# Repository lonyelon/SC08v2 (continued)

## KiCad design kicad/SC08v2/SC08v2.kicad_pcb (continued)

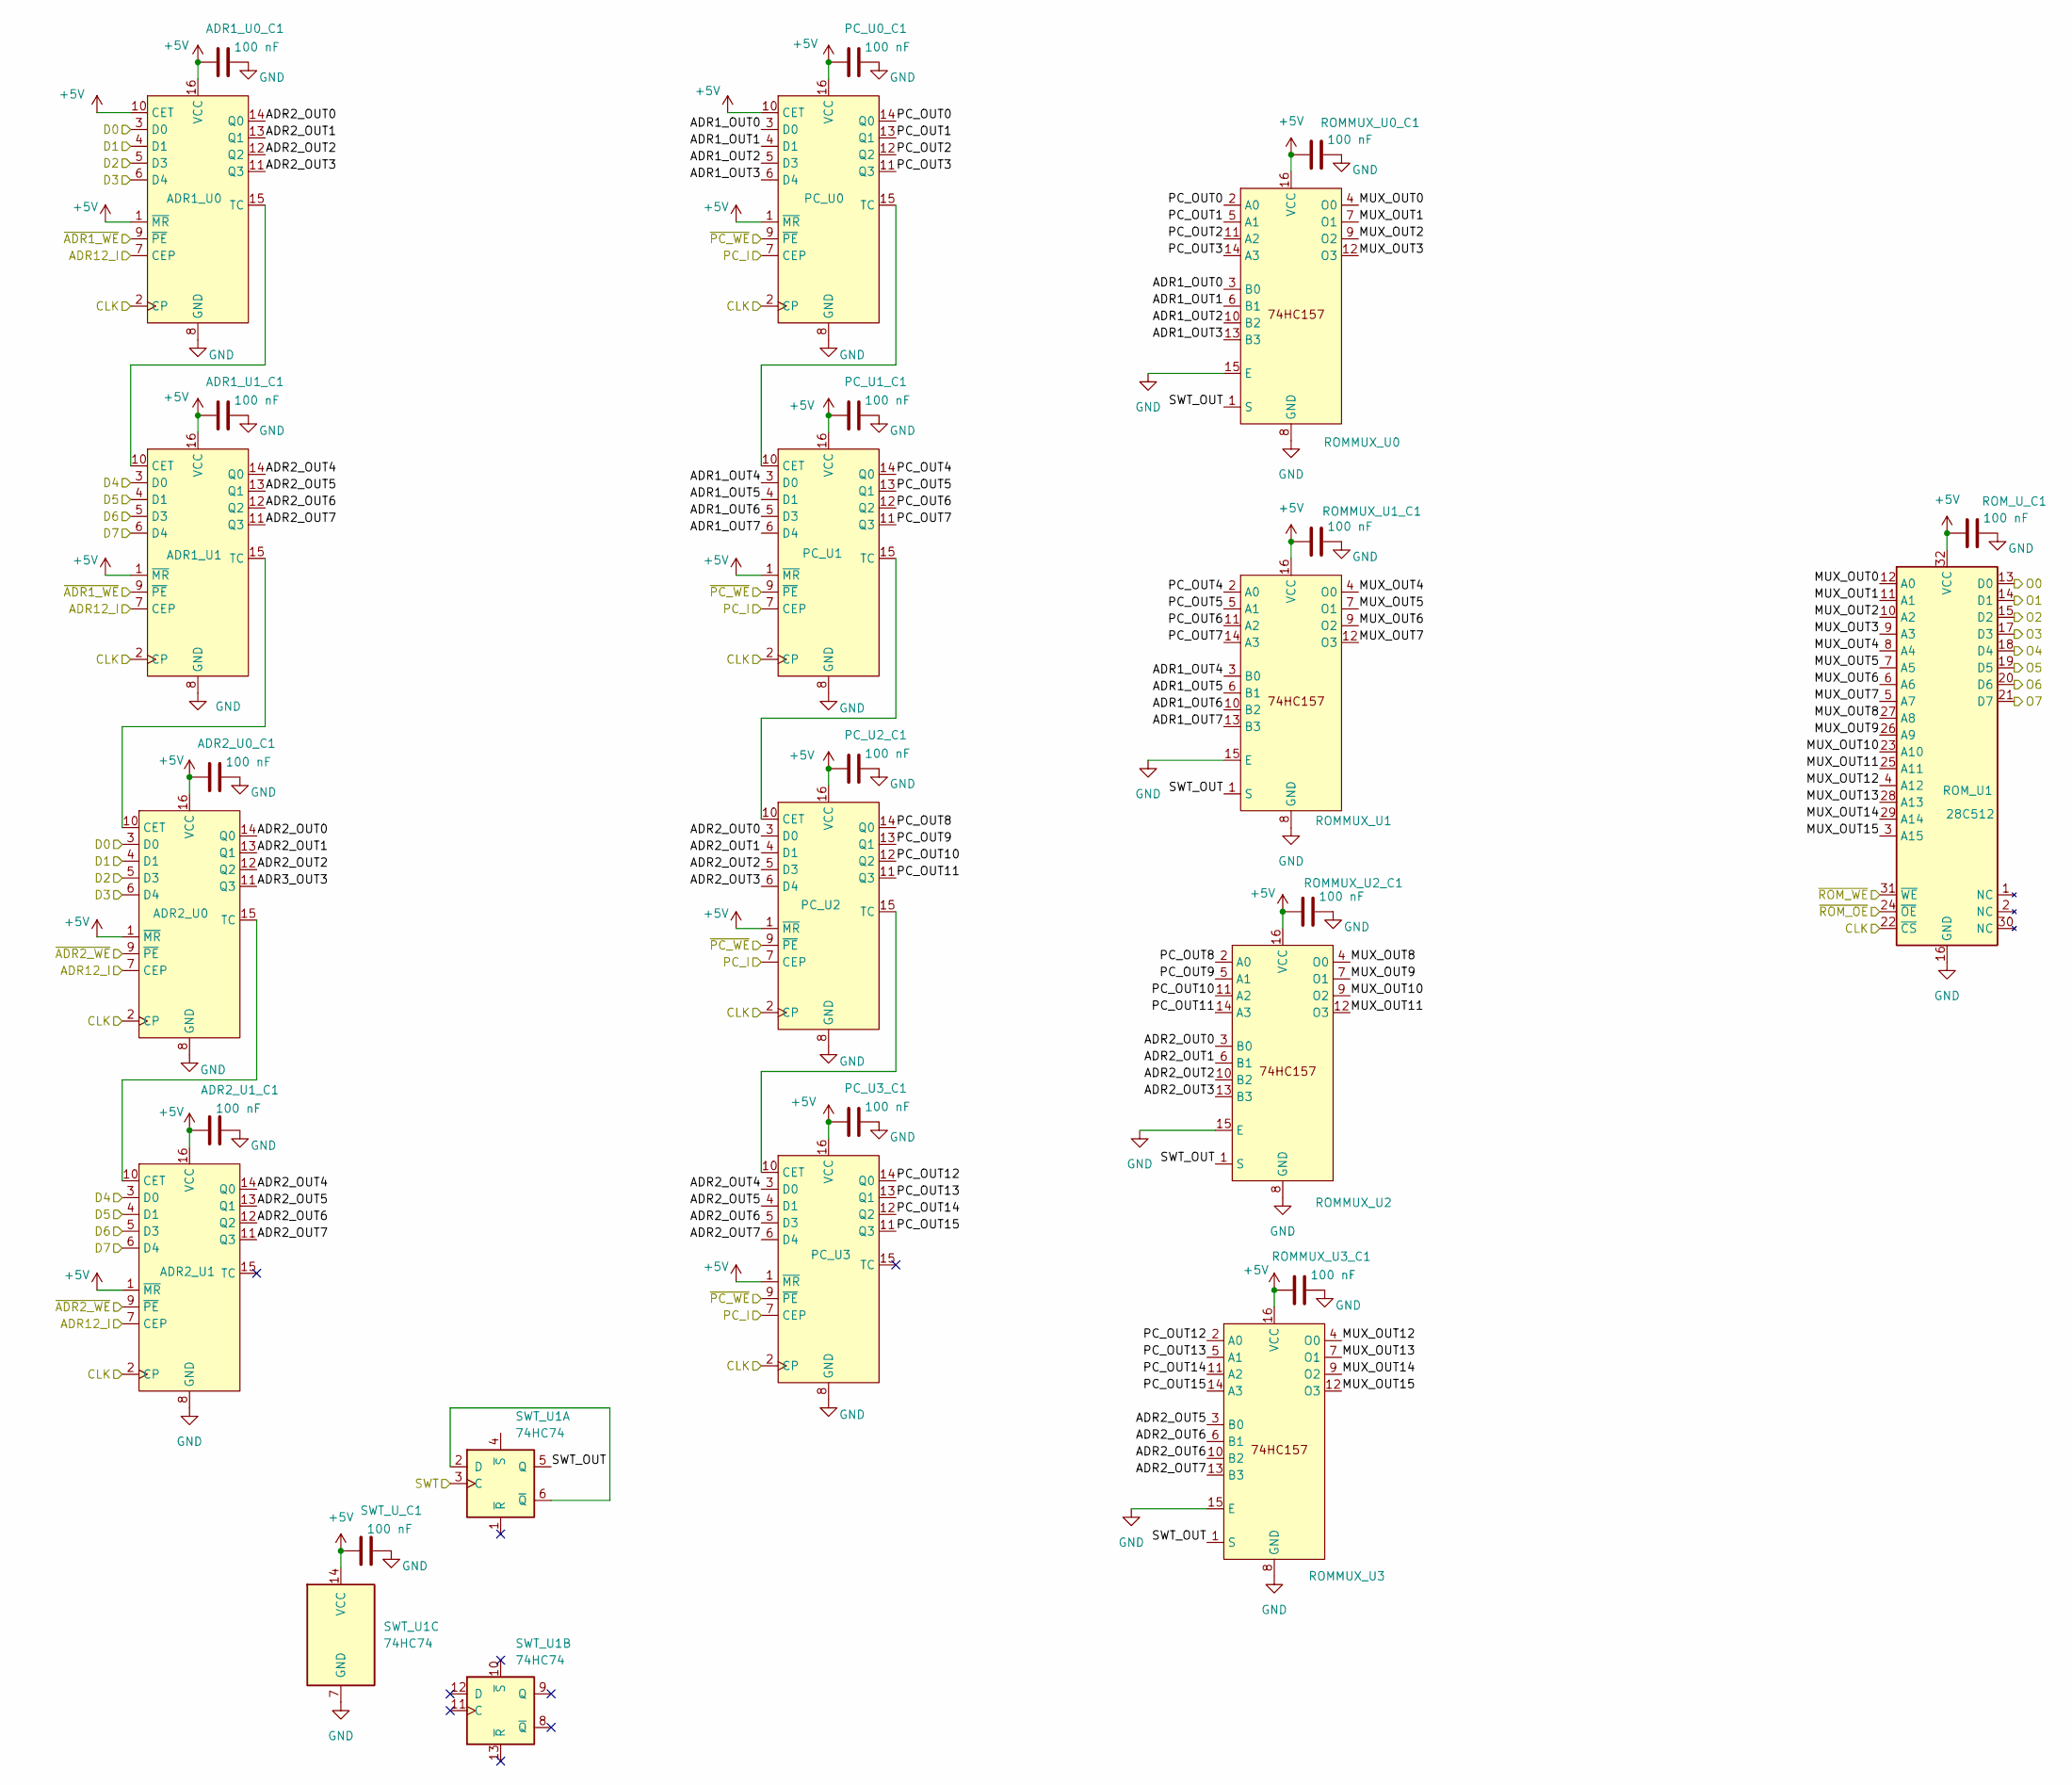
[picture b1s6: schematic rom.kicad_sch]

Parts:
ADR1_U0, ADR1_U1, ADR2_U0, ADR2_U1: DIP-16_W7.62mm
ADR1_U0_C1, ADR1_U1_C1, ADR2_U0_C1, ADR2_U1_C1: 100 nF; C_Disc_D3.0mm_W1.6mm_P2.50mm
PC_U0, PC_U1, PC_U2, PC_U3: DIP-16_W7.62mm
PC_U0_C1, PC_U1_C1, PC_U2_C1, PC_U3_C1: 100 nF; C_Disc_D3.0mm_W1.6mm_P2.50mm
ROMMUX_U0, ROMMUX_U1, ROMMUX_U2, ROMMUX_U3: DIP-16_W7.62mm
ROMMUX_U0_C1, ROMMUX_U1_C1, ROMMUX_U2_C1, ROMMUX_U3_C1: 100 nF; C_Disc_D3.0mm_W1.6mm_P2.50mm
ROM_U1: 28C512; DIP-32_W15.24mm
ROM_U_C1: 100 nF; C_Disc_D3.0mm_W1.6mm_P2.50mm
SWT_U1: 74HC74; DIP-14_W7.62mm
SWT_U_C1: 100 nF; C_Disc_D3.0mm_W1.6mm_P2.50mm

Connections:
+5V: ADR1_U0.1 (~MR), ADR1_U0.10 (CET), ADR1_U0.16 (VCC), ADR1_U0_C1.1, ADR1_U1.1 (~MR), ADR1_U1.16 (VCC), ADR1_U1_C1.1, ADR2_U0.1 (~MR), ADR2_U0.16 (VCC), ADR2_U0_C1.1, ADR2_U1.1 (~MR), ADR2_U1.16 (VCC), ADR2_U1_C1.1, PC_U0.1 (~MR), PC_U0.10 (CET), PC_U0.16 (VCC), PC_U0_C1.1, PC_U1.1 (~MR), PC_U1.16 (VCC), PC_U1_C1.1, PC_U2.1 (~MR), PC_U2.16 (VCC), PC_U2_C1.1, PC_U3.1 (~MR), PC_U3.16 (VCC), PC_U3_C1.1, ROMMUX_U0.16 (VCC), ROMMUX_U0_C1.1, ROMMUX_U1.16 (VCC), ROMMUX_U1_C1.1, ROMMUX_U2.16 (VCC), ROMMUX_U2_C1.1, ROMMUX_U3.16 (VCC), ROMMUX_U3_C1.1, ROM_U1.32 (VCC), ROM_U_C1.1, SWT_U1.14 (VCC), SWT_U_C1.1; also elsewhere on the board
/ADR12_I: ADR1_U0.7 (CEP), ADR1_U1.7 (CEP), ADR2_U0.7 (CEP), ADR2_U1.7 (CEP); also elsewhere on the board
/BUS_0: ADR1_U0.3 (D0), ADR2_U0.3 (D0), ROM_U1.13 (D0); also elsewhere on the board
/BUS_1: ADR1_U0.4 (D1), ADR2_U0.4 (D1), ROM_U1.14 (D1); also elsewhere on the board
/BUS_2: ADR1_U0.5 (D3), ADR2_U0.5 (D3), ROM_U1.15 (D2); also elsewhere on the board
/BUS_3: ADR1_U0.6 (D4), ADR2_U0.6 (D4), ROM_U1.17 (D3); also elsewhere on the board
/BUS_4: ADR1_U1.3 (D0), ADR2_U1.3 (D0), ROM_U1.18 (D4); also elsewhere on the board
/BUS_5: ADR1_U1.4 (D1), ADR2_U1.4 (D1), ROM_U1.19 (D5); also elsewhere on the board
/BUS_6: ADR1_U1.5 (D3), ADR2_U1.5 (D3), ROM_U1.20 (D6); also elsewhere on the board
/BUS_7: ADR1_U1.6 (D4), ADR2_U1.6 (D4), ROM_U1.21 (D7); also elsewhere on the board
/CLK: ADR1_U0.2 (CP), ADR1_U1.2 (CP), ADR2_U0.2 (CP), ADR2_U1.2 (CP), PC_U0.2 (CP), PC_U1.2 (CP), PC_U2.2 (CP), PC_U3.2 (CP), ROM_U1.22 (~CS); also elsewhere on the board
/PC_I: PC_U0.7 (CEP), PC_U1.7 (CEP), PC_U2.7 (CEP), PC_U3.7 (CEP); also elsewhere on the board
/ROM/ADR1_OUT0: PC_U0.3 (D0), ROMMUX_U0.3 (B0)
/ROM/ADR1_OUT1: PC_U0.4 (D1), ROMMUX_U0.6 (B1)
/ROM/ADR1_OUT2: PC_U0.5 (D3), ROMMUX_U0.10 (B2)
/ROM/ADR1_OUT3: PC_U0.6 (D4), ROMMUX_U0.13 (B3)
/ROM/ADR1_OUT4: PC_U1.3 (D0), ROMMUX_U1.3 (B0)
/ROM/ADR1_OUT5: PC_U1.4 (D1), ROMMUX_U1.6 (B1)
/ROM/ADR1_OUT6: PC_U1.5 (D3), ROMMUX_U1.10 (B2)
/ROM/ADR1_OUT7: PC_U1.6 (D4), ROMMUX_U1.13 (B3)
/ROM/ADR2_OUT0: ADR1_U0.14 (Q0), ADR2_U0.14 (Q0), PC_U2.3 (D0), ROMMUX_U2.3 (B0)
/ROM/ADR2_OUT1: ADR1_U0.13 (Q1), ADR2_U0.13 (Q1), PC_U2.4 (D1), ROMMUX_U2.6 (B1)
/ROM/ADR2_OUT2: ADR1_U0.12 (Q2), ADR2_U0.12 (Q2), PC_U2.5 (D3), ROMMUX_U2.10 (B2)
/ROM/ADR2_OUT3: ADR1_U0.11 (Q3), PC_U2.6 (D4), ROMMUX_U2.13 (B3)
/ROM/ADR2_OUT4: ADR1_U1.14 (Q0), ADR2_U1.14 (Q0), PC_U3.3 (D0)
/ROM/ADR2_OUT5: ADR1_U1.13 (Q1), ADR2_U1.13 (Q1), PC_U3.4 (D1), ROMMUX_U3.3 (B0)
/ROM/ADR2_OUT6: ADR1_U1.12 (Q2), ADR2_U1.12 (Q2), PC_U3.5 (D3), ROMMUX_U3.6 (B1), ROMMUX_U3.10 (B2)
/ROM/ADR2_OUT7: ADR1_U1.11 (Q3), ADR2_U1.11 (Q3), PC_U3.6 (D4), ROMMUX_U3.13 (B3)
/ROM/ADR3_OUT3: ADR2_U0.11 (Q3)
/ROM/MUX_OUT0: ROMMUX_U0.4 (O0), ROM_U1.12 (A0)
/ROM/MUX_OUT1: ROMMUX_U0.7 (O1), ROM_U1.11 (A1)
/ROM/MUX_OUT2: ROMMUX_U0.9 (O2), ROM_U1.10 (A2)
/ROM/MUX_OUT3: ROMMUX_U0.12 (O3), ROM_U1.9 (A3)
/ROM/MUX_OUT4: ROMMUX_U1.4 (O0), ROM_U1.8 (A4)
/ROM/MUX_OUT5: ROMMUX_U1.7 (O1), ROM_U1.7 (A5)
/ROM/MUX_OUT6: ROMMUX_U1.9 (O2), ROM_U1.6 (A6)
/ROM/MUX_OUT7: ROMMUX_U1.12 (O3), ROM_U1.5 (A7)
/ROM/MUX_OUT8: ROMMUX_U2.4 (O0), ROM_U1.27 (A8)
/ROM/MUX_OUT9: ROMMUX_U2.7 (O1), ROM_U1.26 (A9)
/ROM/MUX_OUT10: ROMMUX_U2.9 (O2), ROM_U1.23 (A10)
/ROM/MUX_OUT11: ROMMUX_U2.12 (O3), ROM_U1.25 (A11)
/ROM/MUX_OUT12: ROMMUX_U3.4 (O0), ROM_U1.4 (A12)
/ROM/MUX_OUT13: ROMMUX_U3.7 (O1), ROM_U1.28 (A13)
/ROM/MUX_OUT14: ROMMUX_U3.9 (O2), ROM_U1.29 (A14)
/ROM/MUX_OUT15: ROMMUX_U3.12 (O3), ROM_U1.3 (A15)
/ROM/PC_OUT0: PC_U0.14 (Q0), ROMMUX_U0.2 (A0)
/ROM/PC_OUT1: PC_U0.13 (Q1), ROMMUX_U0.5 (A1)
/ROM/PC_OUT2: PC_U0.12 (Q2), ROMMUX_U0.11 (A2)
/ROM/PC_OUT3: PC_U0.11 (Q3), ROMMUX_U0.14 (A3)
/ROM/PC_OUT4: PC_U1.14 (Q0), ROMMUX_U1.2 (A0)
/ROM/PC_OUT5: PC_U1.13 (Q1), ROMMUX_U1.5 (A1)
/ROM/PC_OUT6: PC_U1.12 (Q2), ROMMUX_U1.11 (A2)
/ROM/PC_OUT7: PC_U1.11 (Q3), ROMMUX_U1.14 (A3)
/ROM/PC_OUT8: PC_U2.14 (Q0), ROMMUX_U2.2 (A0)
/ROM/PC_OUT9: PC_U2.13 (Q1), ROMMUX_U2.5 (A1)
/ROM/PC_OUT10: PC_U2.12 (Q2), ROMMUX_U2.11 (A2)
/ROM/PC_OUT11: PC_U2.11 (Q3), ROMMUX_U2.14 (A3)
/ROM/PC_OUT12: PC_U3.14 (Q0), ROMMUX_U3.2 (A0)
/ROM/PC_OUT13: PC_U3.13 (Q1), ROMMUX_U3.5 (A1)
/ROM/PC_OUT14: PC_U3.12 (Q2), ROMMUX_U3.11 (A2)
/ROM/PC_OUT15: PC_U3.11 (Q3), ROMMUX_U3.14 (A3)
/ROM/SWT_OUT: ROMMUX_U0.1 (S), ROMMUX_U1.1 (S), ROMMUX_U2.1 (S), ROMMUX_U3.1 (S), SWT_U1.5 (Q)
/SWT: SWT_U1.3 (C); also elsewhere on the board
/~ADR1_WE: ADR1_U0.9 (~PE), ADR1_U1.9 (~PE); also elsewhere on the board
/~ADR2_WE: ADR2_U0.9 (~PE), ADR2_U1.9 (~PE); also elsewhere on the board
/~PC_WE: PC_U0.9 (~PE), PC_U1.9 (~PE), PC_U2.9 (~PE), PC_U3.9 (~PE); also elsewhere on the board
/~ROM_OE: ROM_U1.24 (~OE); also elsewhere on the board
/~ROM_WE: ROM_U1.31 (~WE); also elsewhere on the board
GND: ADR1_U0.8 (GND), ADR1_U0_C1.2, ADR1_U1.8 (GND), ADR1_U1_C1.2, ADR2_U0.8 (GND), ADR2_U0_C1.2, ADR2_U1.8 (GND), ADR2_U1_C1.2, PC_U0.8 (GND), PC_U0_C1.2, PC_U1.8 (GND), PC_U1_C1.2, PC_U2.8 (GND), PC_U2_C1.2, PC_U3.8 (GND), PC_U3_C1.2, ROMMUX_U0.8 (GND), ROMMUX_U0.15 (E), ROMMUX_U0_C1.2, ROMMUX_U1.8 (GND), ROMMUX_U1.15 (E), ROMMUX_U1_C1.2, ROMMUX_U2.8 (GND), ROMMUX_U2.15 (E), ROMMUX_U2_C1.2, ROMMUX_U3.8 (GND), ROMMUX_U3.15 (E), ROMMUX_U3_C1.2, ROM_U1.16 (GND), ROM_U_C1.2, SWT_U1.7 (GND), SWT_U_C1.2; also elsewhere on the board
unnamed: ADR1_U0.15 (TC), ADR1_U1.10 (CET)
unnamed: ADR1_U1.15 (TC), ADR2_U0.10 (CET)
unnamed: ADR2_U0.15 (TC), ADR2_U1.10 (CET)
unnamed: PC_U0.15 (TC), PC_U1.10 (CET)
unnamed: PC_U1.15 (TC), PC_U2.10 (CET)
unnamed: PC_U2.15 (TC), PC_U3.10 (CET)
unnamed: SWT_U1.2 (D), SWT_U1.6 (~Q)

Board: 4 copper layers, 116 parts (0 on the bottom side), 197 nets, no tracks yet.

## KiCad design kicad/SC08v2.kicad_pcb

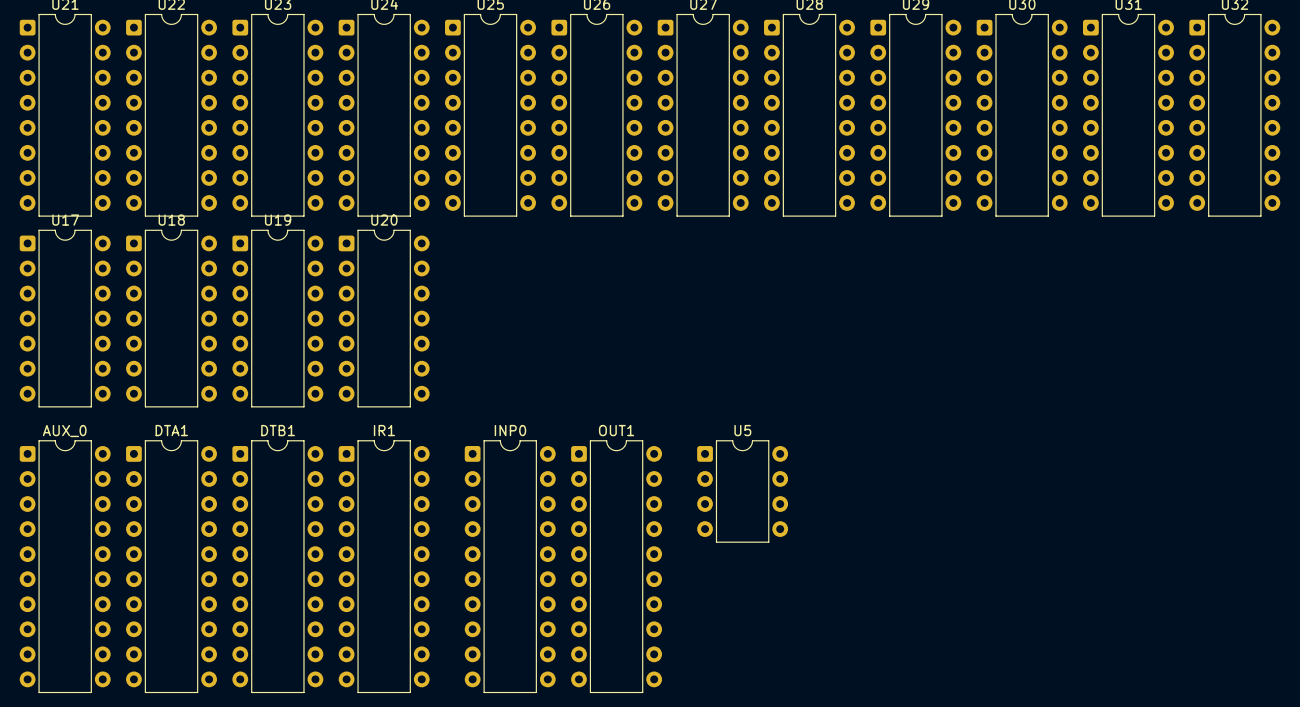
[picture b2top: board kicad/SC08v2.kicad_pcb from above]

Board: 2 copper layers, 23 parts (0 on the bottom side), 63 nets, no tracks yet.

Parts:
AUX_0: 74HC273; DIP-20_W7.62mm
DTA1: 74HC273; DIP-20_W7.62mm
DTB1: 74HC273; DIP-20_W7.62mm
INP0: 74HC273; DIP-20_W7.62mm
IR1: 74HC273; DIP-20_W7.62mm
OUT1: 74HC273; DIP-20_W7.62mm
U5: LM555xN; DIP-8_W7.62mm
U17, U18: 74HC86; DIP-14_W7.62mm
U19, U20: 74HC00; DIP-14_W7.62mm
U21, U22: 74HC85; DIP-16_W7.62mm
U23, U26: 74HC283; DIP-16_W7.62mm
U24, U25, U27, U28, U29, U30, U31, U32: 74HC151; DIP-16_W7.62mm

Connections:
+5V: AUX_0.20 (VCC), DTA1.20 (VCC), DTB1.20 (VCC), INP0.20 (VCC), IR1.20 (VCC), OUT1.20 (VCC), U5.4 (R), U5.8 (VCC), U17.14 (VCC), U18.14 (VCC), U19.14 (VCC), U20.14 (VCC), U21.16 (VCC), U22.16 (VCC), U23.16 (VCC), U24.16 (VCC), U25.16 (VCC), U26.16 (VCC), U27.16 (VCC), U28.16 (VCC), U29.16 (VCC), U30.16 (VCC), U31.16 (VCC), U32.16 (VCC)
/ALU/A0: DTA1.2 (Q0), U19.1, U21.15 (A3), U23.5 (A1), U24.4 (I0), U27.13 (I6)
/ALU/A1: DTA1.5 (Q1), U19.4, U21.13 (A2), U23.3 (A2), U24.12 (I7), U27.4 (I0), U29.13 (I6)
/ALU/A2: DTA1.6 (Q2), U19.9, U21.12 (A1), U23.14 (A3), U27.12 (I7), U29.4 (I0), U31.13 (I6)
/ALU/A3: DTA1.9 (Q3), U19.12, U21.10 (A0), U23.12 (A4), U25.13 (I6), U29.12 (I7), U31.4 (I0)
/ALU/A4: DTA1.12 (Q4), U20.1, U22.15 (A3), U25.4 (I0), U26.5 (A1), U28.13 (I6), U31.12 (I7)
/ALU/A5: DTA1.15 (Q5), U20.4, U22.13 (A2), U25.12 (I7), U26.3 (A2), U28.4 (I0), U30.13 (I6)
/ALU/A6: DTA1.16 (Q6), U20.9, U22.12 (A1), U26.14 (A3), U28.12 (I7), U30.4 (I0), U32.13 (I6)
/ALU/A7: DTA1.19 (Q7), U20.12, U22.10 (A0), U26.12 (A4), U30.12 (I7), U32.4 (I0)
/ALU/B0: DTB1.2 (Q0), U17.1, U19.2, U21.1 (B3)
/ALU/B1: DTB1.5 (Q1), U17.4, U19.5, U21.14 (B2)
/ALU/B2: DTB1.6 (Q2), U17.9, U19.10, U21.11 (B1)
/ALU/B3: DTB1.9 (Q3), U17.12, U19.13, U21.9 (B0)
/ALU/B4: DTB1.12 (Q4), U18.1, U20.2, U22.1 (B3)
/ALU/B5: DTB1.15 (Q5), U18.4, U20.5, U22.14 (B2)
/ALU/B6: DTB1.16 (Q6), U18.9, U20.10, U22.11 (B1)
/ALU/B7: DTB1.19 (Q7), U18.12, U20.13, U22.9 (B0)
/ALU/XOR_0: U17.3, U23.6 (B1)
/ALU/XOR_1: U17.6, U23.2 (B2)
/ALU/XOR_2: U17.8, U23.15 (B3)
/ALU/XOR_3: U17.11, U23.11 (B4)
/ALU/XOR_4: U18.3, U26.6 (B1)
/ALU/XOR_5: U18.6, U26.2 (B2)
/ALU/XOR_6: U18.8, U26.15 (B3)
/ALU/XOR_7: U18.11, U26.11 (B4)
/ALU/add_out_0: U23.4 (S1), U24.1 (I3), U24.2 (I2)
/ALU/add_out_1: U23.1 (S2), U27.1 (I3), U27.2 (I2)
/ALU/add_out_2: U23.13 (S3), U29.1 (I3), U29.2 (I2)
/ALU/add_out_3: U23.10 (S4), U31.1 (I3), U31.2 (I2)
/ALU/add_out_4: U25.1 (I3), U25.2 (I2), U26.4 (S1)
/ALU/add_out_5: U26.1 (S2), U28.1 (I3), U28.2 (I2)
/ALU/add_out_6: U26.13 (S3), U30.1 (I3), U30.2 (I2)
/ALU/add_out_7: U26.10 (S4), U32.1 (I3), U32.2 (I2)
/ALU/equ_internal: U21.6 (Oa=b), U22.3 (Ia=b)
/ALU/equ_out: U22.6 (Oa=b), U24.15 (I4), U25.15 (I4), U27.15 (I4), U28.15 (I4), U29.15 (I4), U30.15 (I4), U31.15 (I4), U32.15 (I4)
/ALU/gre_internal: U21.5 (Oa>b), U22.4 (Ia>b)
/ALU/gre_out: U22.5 (Oa>b), U24.14 (I5), U25.14 (I5), U27.14 (I5), U28.14 (I5), U29.14 (I5), U30.14 (I5), U31.14 (I5), U32.14 (I5)
/ALU/low_internal: U21.7 (Oa<b), U22.2 (Ia<b)
/ALU/nand_out_0: U19.3, U24.3 (I1)
/ALU/nand_out_1: U19.6, U27.3 (I1)
/ALU/nand_out_2: U19.8, U29.3 (I1)
/ALU/nand_out_3: U19.11, U31.3 (I1)
/ALU/nand_out_4: U20.3, U25.3 (I1)
/ALU/nand_out_5: U20.6, U28.3 (I1)
/ALU/nand_out_6: U20.8, U30.3 (I1)
/ALU/nand_out_7: U20.11, U32.3 (I1)
/ALU/~OE: U24.7 (~E), U25.7 (~E), U27.7 (~E), U28.7 (~E), U29.7 (~E), U30.7 (~E), U31.7 (~E), U32.7 (~E)
/BUS_0: AUX_0.3 (D0), DTA1.3 (D0), DTB1.3 (D0), IR1.3 (D0), OUT1.3 (D0), U24.5 (Z)
/BUS_1: AUX_0.4 (D1), DTA1.4 (D1), DTB1.4 (D1), IR1.4 (D1), OUT1.4 (D1), U27.5 (Z)
/BUS_2: AUX_0.7 (D2), DTA1.7 (D2), DTB1.7 (D2), IR1.7 (D2), OUT1.7 (D2), U29.5 (Z)
/BUS_3: AUX_0.8 (D3), DTA1.8 (D3), DTB1.8 (D3), IR1.8 (D3), OUT1.8 (D3), U31.5 (Z)
/BUS_4: AUX_0.13 (D4), DTA1.13 (D4), DTB1.13 (D4), IR1.13 (D4), OUT1.13 (D4), U25.5 (Z)
/BUS_5: AUX_0.14 (D5), DTA1.14 (D5), DTB1.14 (D5), IR1.14 (D5), OUT1.14 (D5), U28.5 (Z)
/BUS_6: AUX_0.17 (D6), DTA1.17 (D6), DTB1.17 (D6), IR1.17 (D6), OUT1.17 (D6), U30.5 (Z)
/BUS_7: AUX_0.18 (D7), DTA1.18 (D7), DTB1.18 (D7), IR1.18 (D7), OUT1.18 (D7), U32.5 (Z)
/CLK: AUX_0.11 (Cp), DTA1.11 (Cp), DTB1.11 (Cp), IR1.11 (Cp), OUT1.11 (Cp), U5.3 (Q)
/IR_OUT_2: IR1.6 (Q2), U24.11 (S0), U25.11 (S0), U27.11 (S0), U28.11 (S0), U29.11 (S0), U30.11 (S0), U31.11 (S0), U32.11 (S0)
/IR_OUT_3: IR1.9 (Q3), U24.10 (S1), U25.10 (S1), U27.10 (S1), U28.10 (S1), U29.10 (S1), U30.10 (S1), U31.10 (S1), U32.10 (S1)
/IR_OUT_4: IR1.12 (Q4), U17.2, U17.5, U17.10, U17.13, U18.2, U18.5, U18.10, U18.13, U24.9 (S2), U25.9 (S2), U27.9 (S2), U28.9 (S2), U29.9 (S2), U30.9 (S2), U31.9 (S2), U32.9 (S2)
/~OUT_WE: AUX_0.1 (~Mr), OUT1.1 (~Mr)
GND: AUX_0.10 (GND), DTA1.10 (GND), DTB1.10 (GND), INP0.10 (GND), IR1.10 (GND), OUT1.10 (GND), U5.1 (GND), U17.7 (GND), U18.7 (GND), U19.7 (GND), U20.7 (GND), U21.8 (GND), U22.8 (GND), U23.7 (C0), U23.8 (GND), U24.8 (GND), U24.13 (I6), U25.8 (GND), U26.8 (GND), U26.9 (C4), U27.8 (GND), U28.8 (GND), U29.8 (GND), U30.8 (GND), U31.8 (GND), U32.8 (GND), U32.12 (I7)
unnamed: U5.2 (TR), U5.6 (THR)
unnamed: U23.9 (C4), U26.7 (C0)

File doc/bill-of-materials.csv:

Material, Count, Price per unit, Total, Link
28C64,        3,              0,      ,
28C512,       3,              0,      ,
74HC00,       2,              0,      ,
74HC85,       2,              0,      ,
74HC86,       2,              0,      ,
74HC151,      8,              0,      ,
74HC273,      2,              0,      ,
74HC283,      2,              0,      ,

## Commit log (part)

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2022-10-13 Add simulator
2022-10-13 Add compiler script
2022-10-15 sim: Add LDD.rom instruction
2022-10-15 sim: Clean and order instructions
2022-10-16 sim: Add ALU instructions and jump test
2022-10-16 sim: fix gitignore
2022-10-16 micro: Add microcode building files
2022-10-16 Add README.md
2022-10-16 sim: Add ALU.num instructions
2022-10-16 asm: Add SO files and tidy up
2022-10-16 doc: Add arch.img
2022-10-16 sim: Add LDD.inp instruction
2022-10-16 asm: Add multiplication test program
2022-10-16 comp: Move compiler.py to a separate directory
2022-10-17 sim: Wrap all cpu elements to allow intentional overflow
2022-10-17 asm: Make multiplication a two bit operation
2022-10-17 Add execution instructions to README.md
2022-10-17 comp: Allow for values to be in base 10
    I got tired of oly using hex values :)
2022-10-17 comp: Add LDD.prr and STD.prr instructions
2022-10-17 sim: Add LDD.ptr and STD.ptr instructions
2022-10-17 comp: Add prr modifier
2022-10-17 asm: Fix LDD instructions
2022-10-17 comp: Fix regular expressions
2022-10-18 asm: Fix multiplication test program
2022-10-18 comp: Compiler was technically and assembler
2022-10-19 comp: Allow to split rom positions
2022-10-19 asm: Add fibbo.asm test program
2022-10-19 comp: Fix regex
2022-10-20 comp: Change notation for ROM addresses
2022-10-20 doc: Add programmer's manual
2025-09-02 Rename directories
2025-09-04 Add compiler
2025-09-16 Add KiCAD files and instructions manual
2025-09-16 Rename ssc08v2 to SC08v2
2025-09-17 Add stack drawio diagram
2025-09-17 kicad: compact design
2025-09-18 kicad: finalize sketch
2025-09-18 Add eeprom-flasher KiCAD files
